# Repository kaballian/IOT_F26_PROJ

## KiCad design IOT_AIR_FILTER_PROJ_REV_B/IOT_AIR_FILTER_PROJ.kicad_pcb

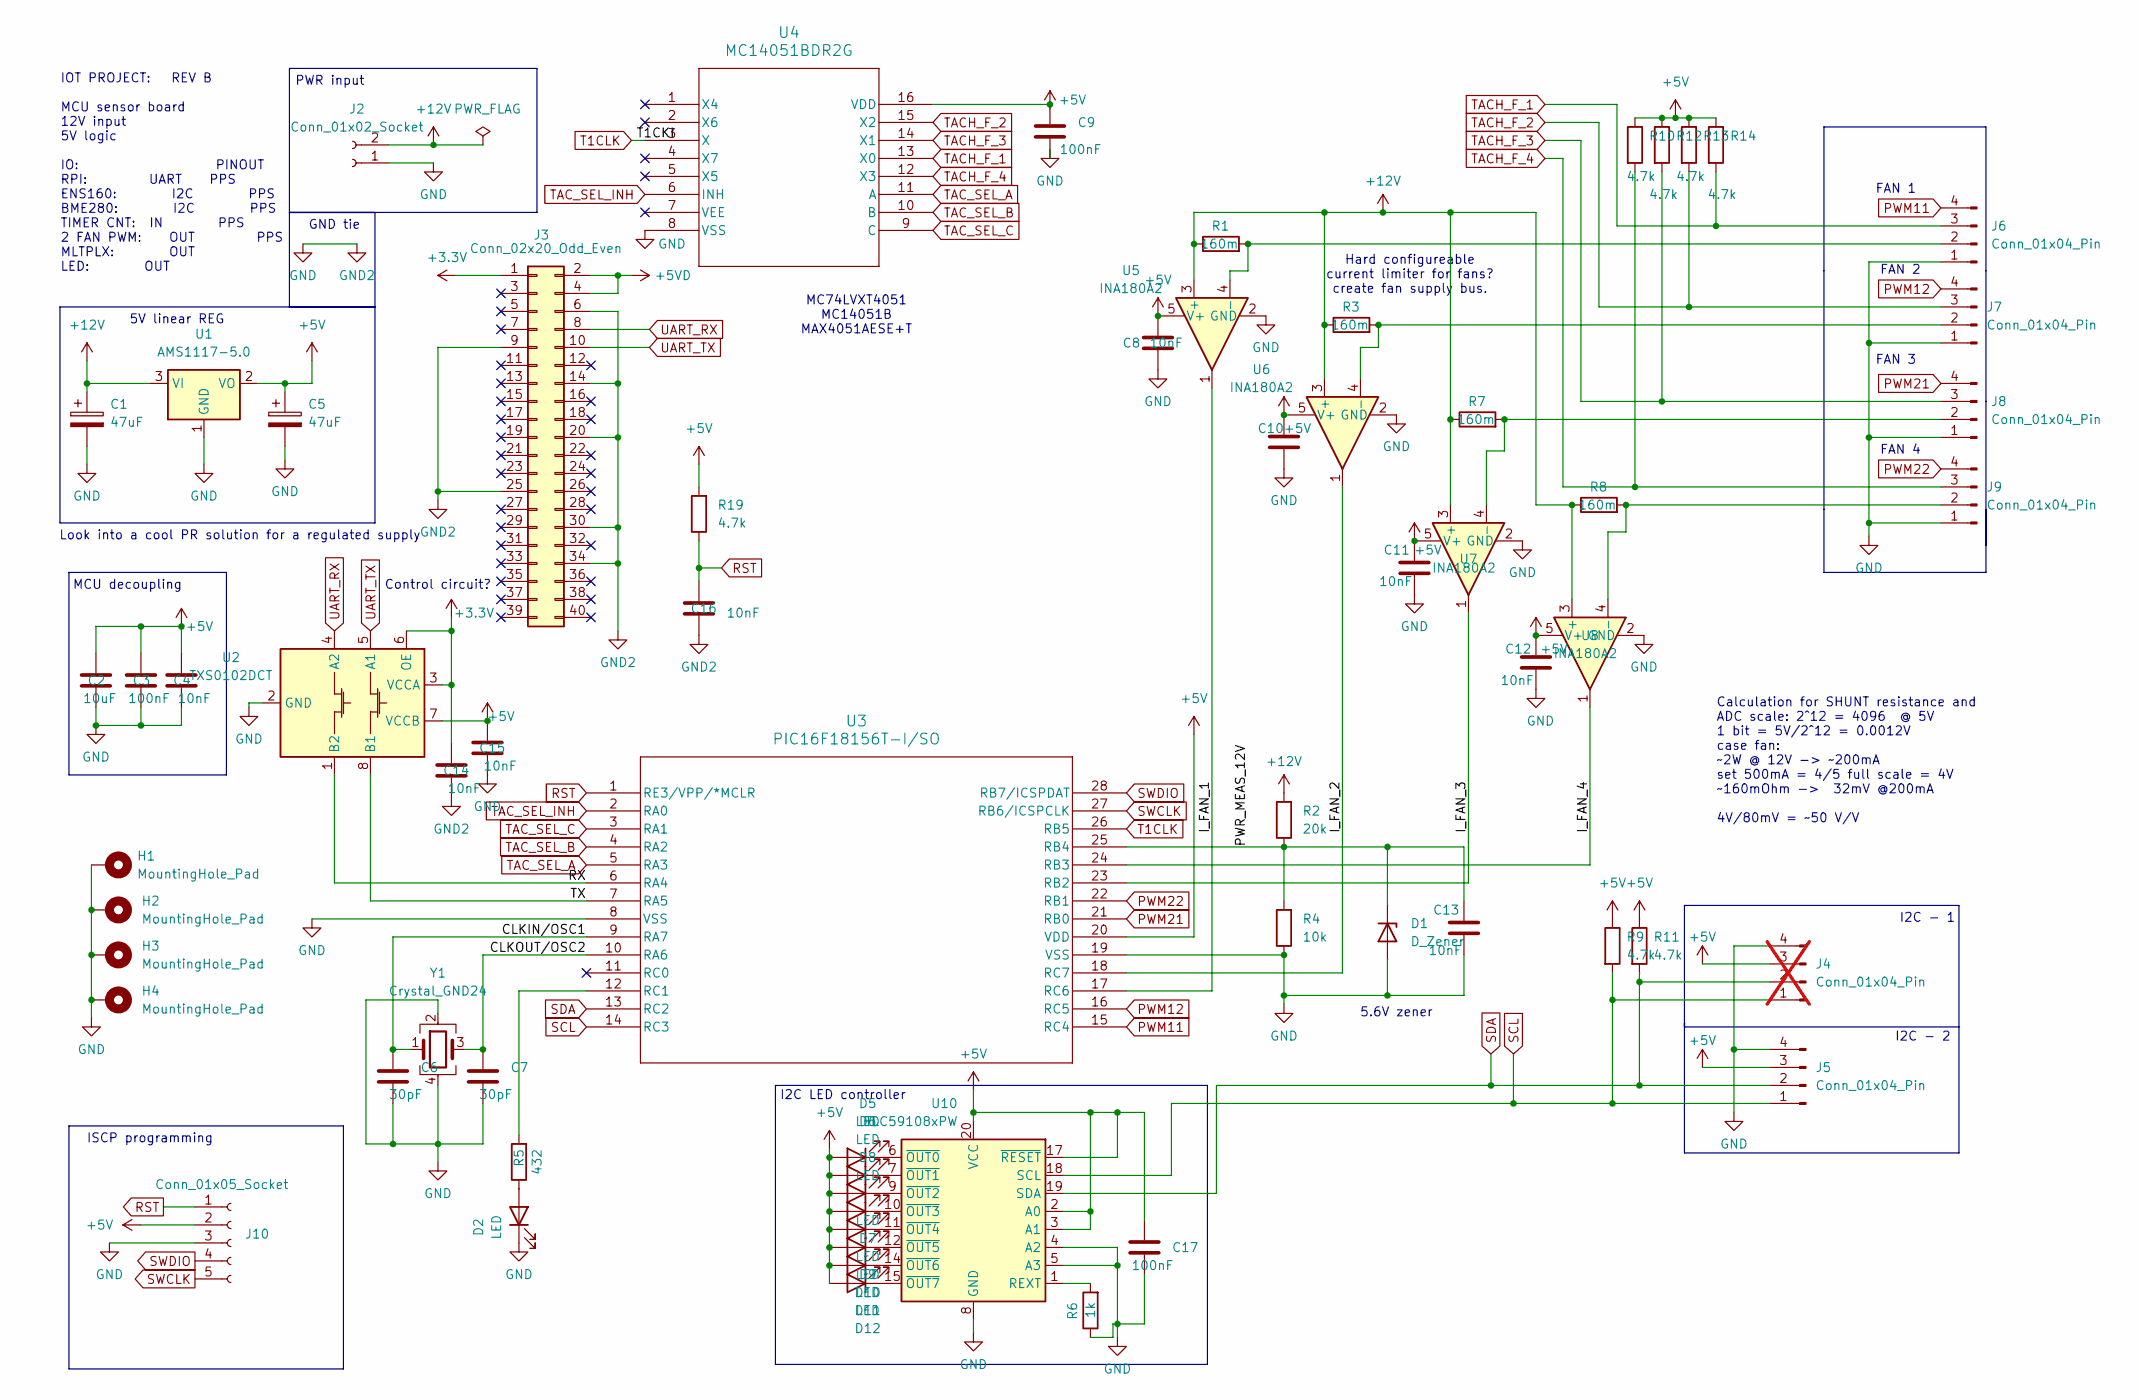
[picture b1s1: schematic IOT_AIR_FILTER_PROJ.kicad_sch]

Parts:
C1, C5: 47uF; CP_Elec_6.3x5.4
C2: 10uF; C_0805_2012Metric
C3, C9, C17: 100nF; C_0805_2012Metric
C4, C8, C10, C11, C12, C13, C14, C15, C16: 10nF; C_0805_2012Metric
C6, C7: 30pF; C_0805_2012Metric
D1: D_Zener; D_SOD-323
D2, D5, D6, D7, D8, D9, D10, D11, D12: LED; LED_0805_2012Metric_Pad1.15x1.40mm_HandSolder
H1, H2, H3, H4: MountingHole_Pad; MountingHole_2.5mm_Pad
J2: Conn_01x02_Socket; PinSocket_1x02_P2.54mm_Horizontal
J3: Conn_02x20_Odd_Even; PinSocket_2x20_P2.54mm_Vertical
J4: Conn_01x04_Pin; JST_GH_SM04B-GHS-TB_1x04-1MP_P1.25mm_Horizontal; not fitted
J5: Conn_01x04_Pin; JST_GH_SM04B-GHS-TB_1x04-1MP_P1.25mm_Horizontal
J6, J7, J8, J9: Conn_01x04_Pin; FanPinHeader_1x04_P2.54mm_Vertical
J10: Conn_01x05_Socket; JST_GH_SM05B-GHS-TB_1x05-1MP_P1.25mm_Horizontal
R1, R3, R7, R8: 160m; R_1210_3225Metric
R2: 20k; R_0805_2012Metric
R4: 10k; R_0805_2012Metric
R5: 432; R_0402_1005Metric
R6: 1k; R_1210_3225Metric
R9, R10, R11, R12, R13, R14, R19: 4.7k; R_0805_2012Metric
U1: AMS1117-5.0; SOT-223-3_TabPin2
U2: TXS0102DCT; SSOP-8_2.95x2.8mm_P0.65mm
U3: PIC16F18156T-I/SO; SOIC28_SO_MCH
U4: MC14051BDR2G; SOIC-16_ONS
U5, U6, U7, U8: INA180A2; SOT-23-5
U10: TLC59108xPW; TSSOP-20_4.4x6.5mm_P0.65mm
Y1: Crystal_GND24; Crystal_SMD_SeikoEpson_FA238-4Pin_3.2x2.5mm_HandSoldering

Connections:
+3.3V: C14.1, J3.1, U2.3 (VCCA), U2.6 (OE)
+5V: C2.1, C3.1, C4.1, C5.1, C8.1, C9.1, C10.1, C11.1, C12.1, C15.1, C17.1, D5.2 (A), D6.2 (A), D7.2 (A), D8.2 (A), D9.2 (A), D10.2 (A), D11.2 (A), D12.2 (A), J4.3, J5.3, J10.2, R9.1, R10.1, R11.1, R12.1, R13.1, R14.1, R19.2, U1.2 (VO), U2.7 (VCCB), U3.20 (VDD), U4.16 (VDD), U5.5 (V+), U6.5 (V+), U7.5 (V+), U8.5 (V+), U10.2 (A0), U10.3 (A1), U10.17 (~RESET), U10.20 (VCC)
+5VD: J3.2, J3.4
+12V: C1.1, J2.2, R1.1, R2.2, R3.1, R7.1, R8.1, U1.3 (VI), U5.3 (+), U6.3 (+), U7.3 (+), U8.3 (+)
/CLKIN/OSC1: C6.1, U3.9 (RA7), Y1.1
/CLKOUT/OSC2: C7.1, U3.10 (RA6), Y1.3
/I_FAN_1: U3.17 (RC6), U5.1
/I_FAN_2: U3.18 (RC7), U6.1
/I_FAN_3: U3.23 (RB2), U7.1
/I_FAN_4: U3.24 (RB3), U8.1
/PWR_MEAS_12V: C13.1, D1.1 (K), R2.1, R4.2, U3.25 (RB4)
/RX: U2.1 (B2), U3.6 (RA4)
/TX: U2.8 (B1), U3.7 (RA5)
GND: C1.2, C2.2, C3.2, C4.2, C5.2, C6.2, C7.2, C8.2, C9.2, C10.2, C11.2, C12.2, C13.2, C14.2, C15.2, C16.2, C17.2, D1.2 (A), D2.1 (K), H1.1, H2.1, H3.1, H4.1, J2.1, J3.6, J3.9, J3.14, J3.20, J3.25, J3.30, J3.34, J4.4, J5.4, J6.1, J7.1, J8.1, J9.1, J10.3, R4.1, R6.1, U1.1 (GND), U2.2 (GND), U3.8 (VSS), U3.19 (VSS), U4.8 (VSS), U5.2 (GND), U6.2 (GND), U7.2 (GND), U8.2 (GND), U10.4 (A2), U10.5 (A3), U10.8 (GND), U10.13 (GND), U10.16 (GND), Y1.2, Y1.4
unnamed: D2.2 (A), R5.1
unnamed: D5.1 (K), U10.6 (~OUT0)
unnamed: D6.1 (K), U10.7 (~OUT1)
unnamed: D7.1 (K), U10.9 (~OUT2)
unnamed: D8.1 (K), U10.10 (~OUT3)
unnamed: D9.1 (K), U10.11 (~OUT4)
unnamed: D10.1 (K), U10.12 (~OUT5)
unnamed: D11.1 (K), U10.14 (~OUT6)
unnamed: D12.1 (K), U10.15 (~OUT7)
unnamed: J6.2, R1.2, U5.4 (-)
unnamed: J7.2, R3.2, U6.4 (-)
unnamed: J8.2, R7.2, U7.4 (-)
unnamed: J9.2, R8.2, U8.4 (-)
unnamed: R5.2, U3.12 (RC1)
unnamed: R6.2, U10.1 (REXT)
PWM11: J6.4, U3.15 (RC4)
PWM12: J7.4, U3.16 (RC5)
PWM21: J8.4, U3.21 (RB0)
PWM22: J9.4, U3.22 (RB1)
RST: C16.1, J10.1, R19.1, U3.1 (RE3/VPP/*MCLR)
SCL: J4.1, J5.1, R9.2, U3.14 (RC3), U10.18 (SCL)
SDA: J4.2, J5.2, R11.2, U3.13 (RC2), U10.19 (SDA)
SWCLK: J10.5, U3.27 (RB6/ICSPCLK)
SWDIO: J10.4, U3.28 (RB7/ICSPDAT)
T1CLK: U3.26 (RB5), U4.3 (X)
TACH_F_1: J6.3, R14.2, U4.13 (X0)
TACH_F_2: J7.3, R13.2, U4.15 (X2)
TACH_F_3: J8.3, R12.2, U4.14 (X1)
TACH_F_4: J9.3, R10.2, U4.12 (X3)
TAC_SEL_A: U3.5 (RA3), U4.11 (A)
TAC_SEL_B: U3.4 (RA2), U4.10 (B)
TAC_SEL_C: U3.3 (RA1), U4.9 (C)
TAC_SEL_INH: U3.2 (RA0), U4.6 (INH)
UART_RX: J3.8, U2.4 (A2)
UART_TX: J3.10, U2.5 (A1)

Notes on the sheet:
GND tie
5.6V zener
Calculation for SHUNT resistance and ADC scale: 2^12 = 4096 @ 5V 1 bit = 5V/2^12 = 0.0012V case fan: ~2W @ 12V -> ~200mA set 500mA = 4/5 full scale = 4V ~160mOhm -> 32mV @200mA 4V/80mV = ~50 V/V
MCU decoupling
FAN 1
FAN 2
FAN 4
5V linear REG
Look into a cool PR solution for a regulated supply
MC74LVXT4051 MC14051B MAX4051AESE+T
PWR input
Control circuit?
Hard configureable current limiter for fans? create fan supply bus.
IOT PROJECT: REV B MCU sensor board 12V input 5V logic IO: PINOUT RPI: UART PPS ENS160: I2C PPS BME280: I2C PPS TIMER CNT: IN PPS 2 FAN PWM: OUT PPS MLTPLX: OUT LED: OUT
I2C - 1
ISCP programming
I2C LED controller
I2C - 2
FAN 3

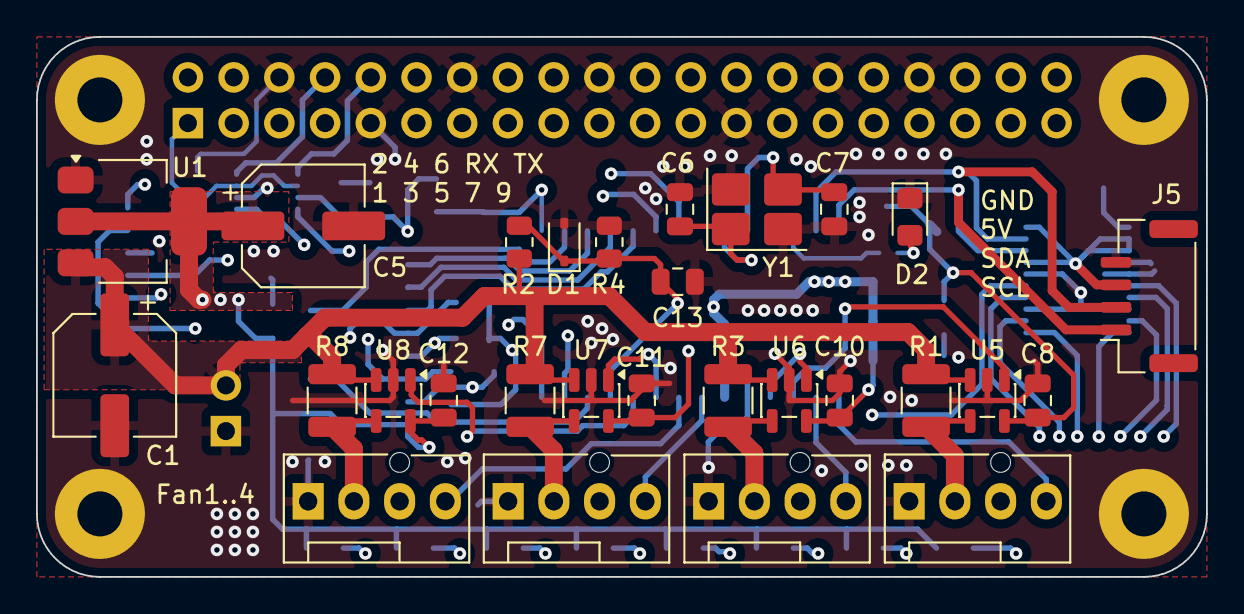
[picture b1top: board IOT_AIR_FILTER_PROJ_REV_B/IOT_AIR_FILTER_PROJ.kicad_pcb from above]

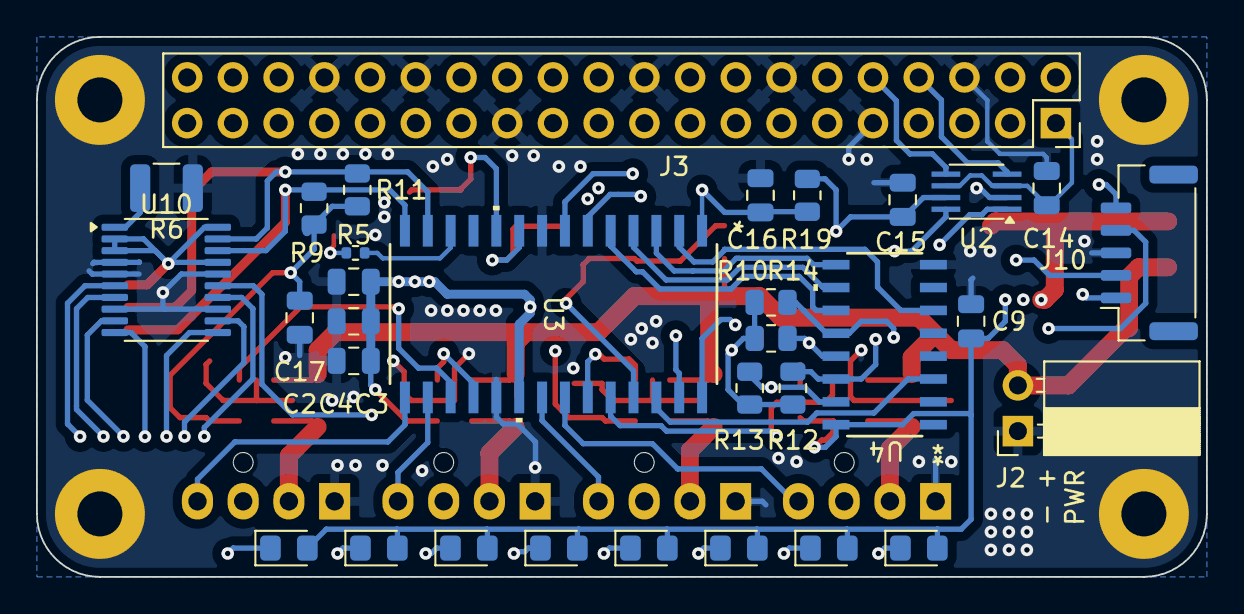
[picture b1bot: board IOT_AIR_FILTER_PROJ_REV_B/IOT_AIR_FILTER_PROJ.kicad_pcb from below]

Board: 4 copper layers, 65.0 x 30.0 mm, 64 parts (32 on the bottom side), 49 nets.

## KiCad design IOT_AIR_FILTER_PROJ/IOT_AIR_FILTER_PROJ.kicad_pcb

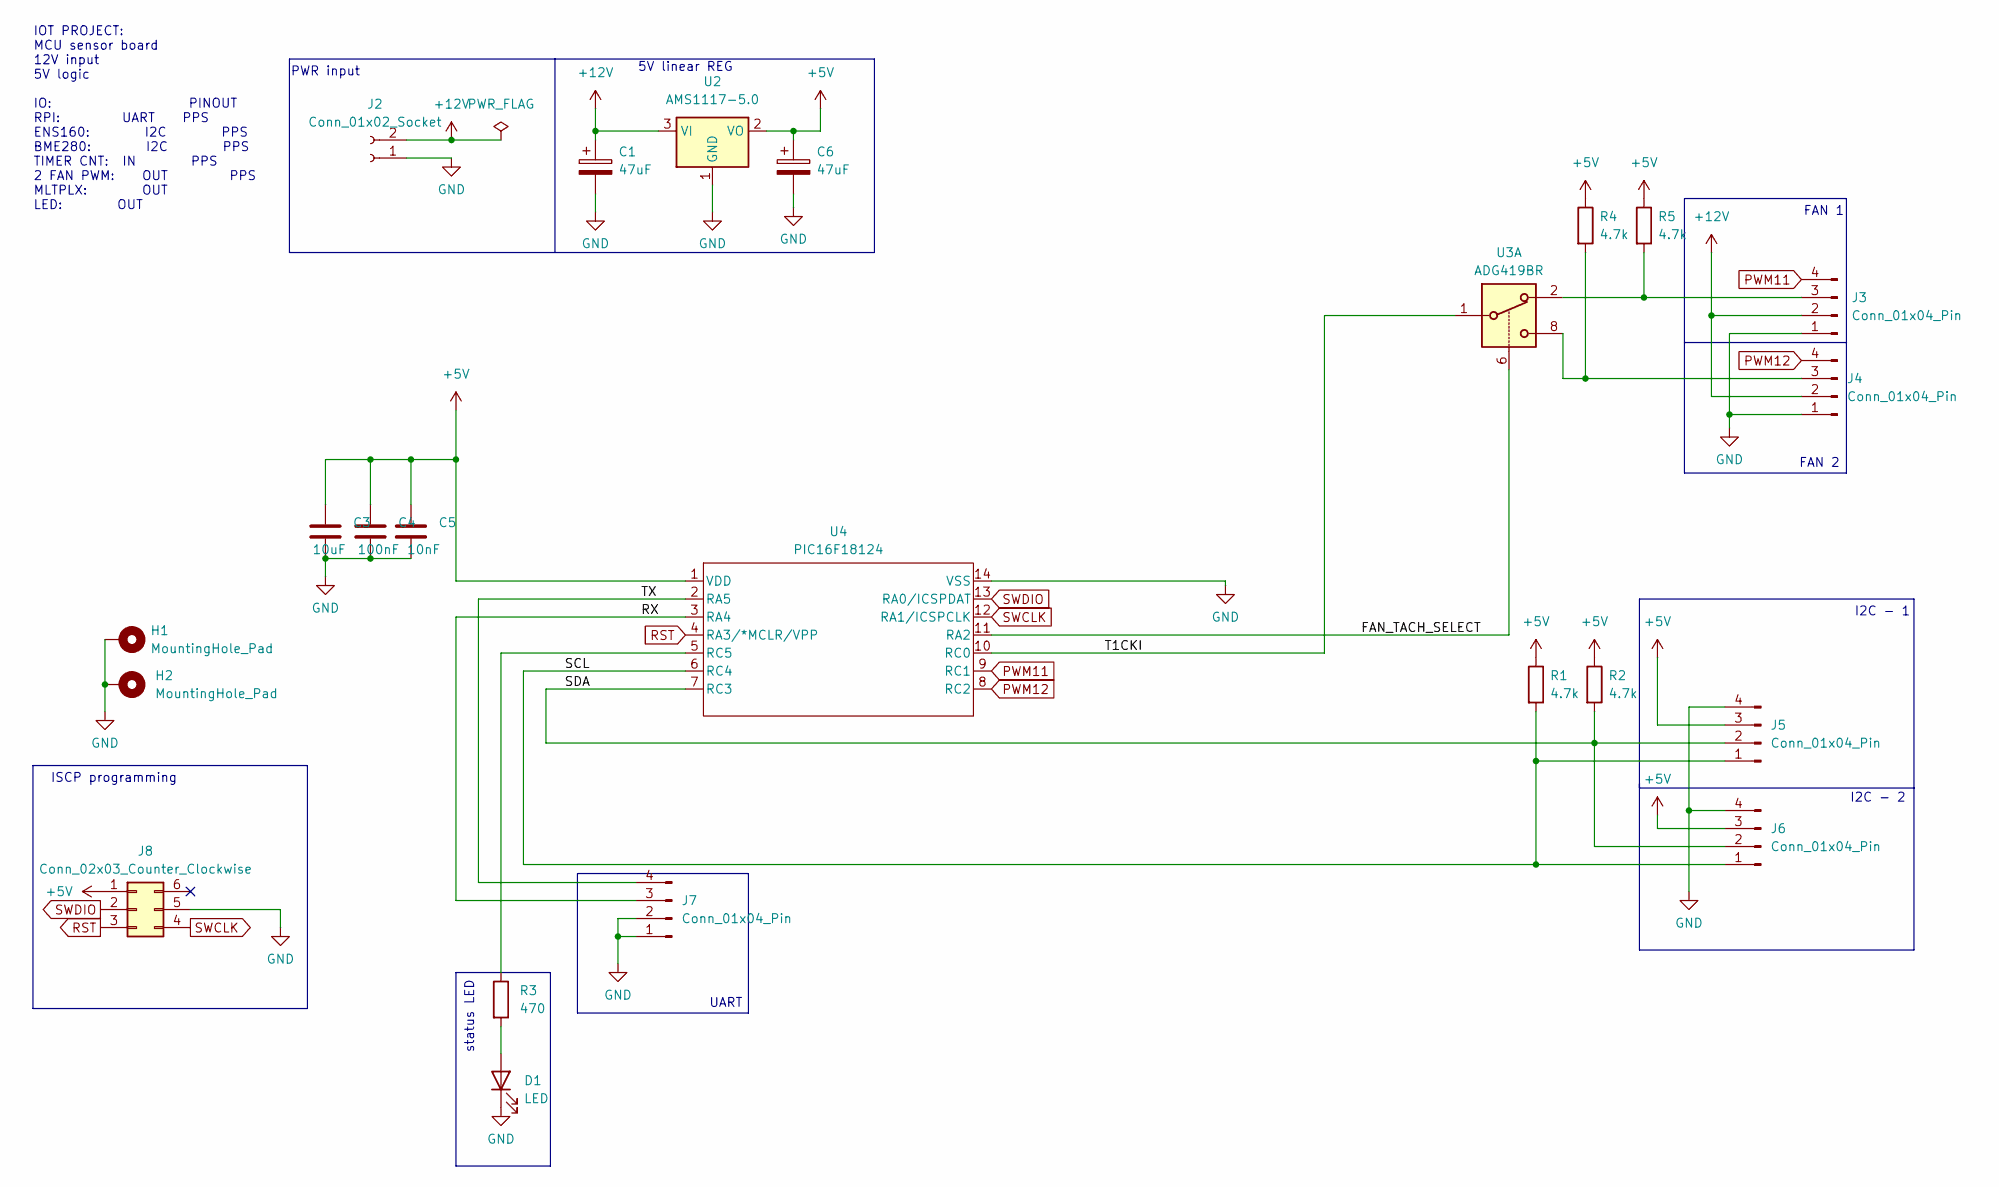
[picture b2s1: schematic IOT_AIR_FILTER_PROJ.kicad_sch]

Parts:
C1, C6: 47uF; CP_Elec_6.3x5.4
C3: 10uF; C_0805_2012Metric
C4: 100nF; C_0805_2012Metric
C5: 10nF; C_0805_2012Metric
D1: LED; LED_0805_2012Metric
H1, H2: MountingHole_Pad; MountingHole_3.2mm_M3_Pad
J2: Conn_01x02_Socket; PinSocket_1x02_P2.54mm_Horizontal
J3, J4: Conn_01x04_Pin; FanPinHeader_1x04_P2.54mm_Vertical
J5, J6, J7: Conn_01x04_Pin; PinHeader_1x04_P2.54mm_Vertical
J8: Conn_02x03_Counter_Clockwise; PinSocket_2x03_P2.54mm_Vertical
R1, R2, R4, R5: 4.7k; R_0805_2012Metric
R3: 470; R_0805_2012Metric
U2: AMS1117-5.0; SOT-223-3_TabPin2
U3: ADG419BR; SOIC-8_3.9x4.9mm_P1.27mm
U4: PIC16F18124; DIP-14_W7.62mm

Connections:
+5V: C3.1, C4.1, C5.1, C6.1, J5.3, J6.3, J8.1, R1.1, R2.1, R4.1, R5.1, U2.2 (VO), U4.1 (VDD)
+12V: C1.1, J2.2, J3.2, J4.2, U2.3 (VI)
/FAN_TACH_SELECT: U3.6, U4.11 (RA2)
/RX: J7.3, U4.3 (RA4)
/SCL: J5.1, J6.1, R1.2, U4.6 (RC4)
/SDA: J5.2, J6.2, R2.2, U4.7 (RC3)
/T1CKI: U3.1, U4.10 (RC0)
/TX: J7.4, U4.2 (RA5)
GND: C1.2, C3.2, C4.2, C5.2, C6.2, D1.1 (K), H1.1, H2.1, J2.1, J3.1, J4.1, J5.4, J6.4, J7.1, J7.2, J8.5, U2.1 (GND), U4.14 (VSS)
unnamed: D1.2 (A), R3.2
unnamed: J3.3, R5.2, U3.2
unnamed: J4.3, R4.2, U3.8
unnamed: R3.1, U4.5 (RC5)
PWM11: J3.4, U4.9 (RC1)
PWM12: J4.4, U4.8 (RC2)
RST: J8.3, U4.4 (RA3/*MCLR/VPP)
SWCLK: J8.4, U4.12 (RA1/ICSPCLK)
SWDIO: J8.2, U4.13 (RA0/ICSPDAT)

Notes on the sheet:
UART
FAN 1
FAN 2
5V linear REG
status LED
PWR input
IOT PROJECT: MCU sensor board 12V input 5V logic IO: PINOUT RPI: UART PPS ENS160: I2C PPS BME280: I2C PPS TIMER CNT: IN PPS 2 FAN PWM: OUT PPS MLTPLX: OUT LED: OUT
I2C - 1
ISCP programming
I2C - 2

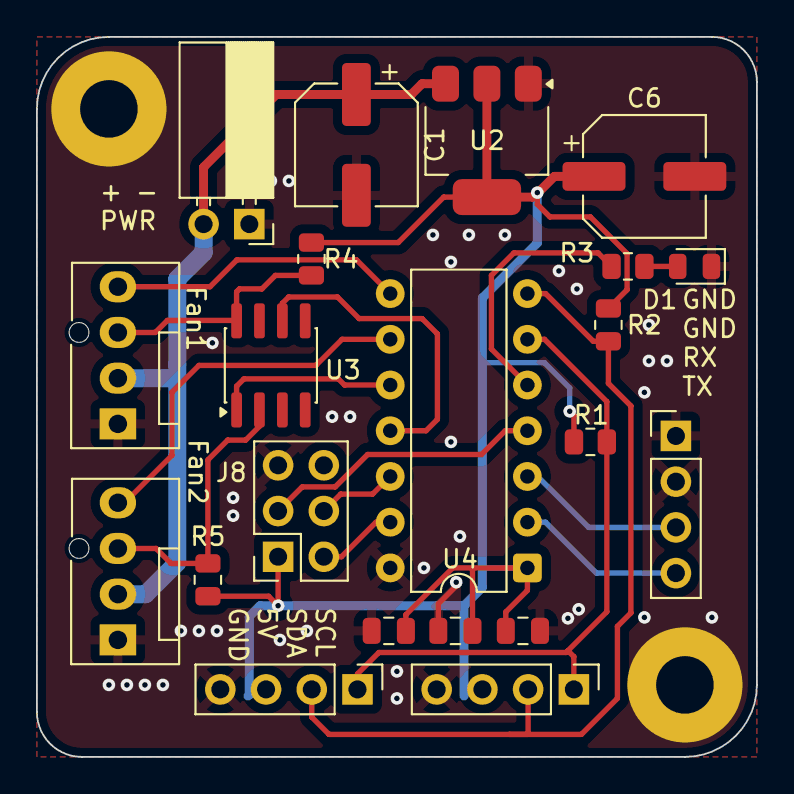
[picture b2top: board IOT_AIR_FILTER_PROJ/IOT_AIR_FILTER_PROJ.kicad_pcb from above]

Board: 2 copper layers, 40.0 x 40.0 mm, 23 parts (0 on the bottom side), 18 nets.

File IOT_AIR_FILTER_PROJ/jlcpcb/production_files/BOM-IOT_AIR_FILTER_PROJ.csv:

Comment,Designator,Footprint,LCSC,Quantity
100nF,C4,C_0805_2012Metric,C49678,1
10nF,C5,C_0805_2012Metric,C1710,1
10uF,C3,C_0805_2012Metric,C440198,1
4.7k,"R1,R2,R4,R5",R_0805_2012Metric,C17673,4
470,R3,R_0805_2012Metric,C17710,1
47uF,"C1,C6",CP_Elec_6.3x5.4,C7469965,2
ADG419BR,U3,SOIC-8_3.9x4.9mm_P1.27mm,C579051,1
AMS1117-5.0,U2,SOT-223-3_TabPin2,C6187,1
LED,D1,LED_0805_2012Metric,C2296,1

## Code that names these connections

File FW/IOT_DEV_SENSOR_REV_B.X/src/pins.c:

#include "include\pins.h"
#include <pic16f18156.h>

void PIN_MANAGER_init(void)
{
    /*LATx registers*/

    LATA = 0x0;
    LATB = 0x0;
    LATC = 0x0;

    /*TRISx registers
    1: input
    0: output
    
    PORT    = |FUNCTION|DIRECTION|VAL|PPS
    RA0     = TAC_SEL_INH   OUT X
    RA1     = TAC_SEL_C     OUT
    RA2     = TAC_SEL_B     OUT
    RA3     = TAC_SEL_A     OUT
    RA4     = RX            IN  1   PPS
    RA5     = TX            OUT 0   PPS

    RB0     = PWM21         OUT 0   PPS
    RB1     = PWM22         OUT 0   PPS
    RB2     = I_FAN_3       IN  1   
    RB3     = I_FAN_4       IN  1
    RB4     = PWR_MEAS_12V  IN  1
    RB5     = T1CLKIN       IN  1   PPS
    
    RC0     = unconnected           
    RC1     = unconnected
    RC2     = I2C SDA       BI      PPS
    RC3     = I2C SCL       BI      PPS
    RC4     = PWM11         OUT 0   PPS
    RC5     = PWM12         OUT 0   PPS
    RC6     = I_FAN_1       IN  1    
    RC7     = I_FAN_2       IN  1


    */

    TRISAbits.TRISA0 = 0;
    TRISAbits.TRISA1 = 0;
    TRISAbits.TRISA2 = 0;
    TRISAbits.TRISA3 = 0;
    TRISAbits.TRISA4 = 1;
    TRISAbits.TRISA5 = 0;

    TRISBbits.TRISB0 = 0;// RB0     = PWM21         OUT 0   PPS
    TRISBbits.TRISB1 = 0;// RB1     = PWM22         OUT 0   PPS
    TRISBbits.TRISB2 = 1;// RB2     = I_FAN_3       IN  1   
    TRISBbits.TRISB3 = 1;// RB3     = I_FAN_4       IN  1
    TRISBbits.TRISB4 = 1;// RB4     = PWR_MEAS_12V  IN  1
    TRISBbits.TRISB5 = 1;// RB5     = T1CLKIN       IN  1   PPS
    
    // TRISCbits.TRISC// RC0     = unconnected  MAKE HI Z           
    // TRISCbits.TRISC// RC1     = unconnected  MAKE HI Z
    TRISCbits.TRISC2 = 1;// RC2     = I2C SDA       BI      PPS
    TRISCbits.TRISC3 = 1;// RC3     = I2C SCL       BI      PPS
    TRISCbits.TRISC4 = 0;// RC4     = PWM11         OUT 0   PPS
    TRISCbits.TRISC5 = 0;// RC5     = PWM12         OUT 0   PPS
    TRISCbits.TRISC6 = 1;// RC6     = I_FAN_1       IN  1    
    TRISCbits.TRISC7 = 1;// RC7     = I_FAN_2       IN  1

    /*ANSELx registers
    analog control
    1 = analog input
    0 = digital i/o*/
    ANSELAbits.ANSELA0 = 0;
    ANSELAbits.ANSELA1 = 0;
    ANSELAbits.ANSELA2 = 0;
    ANSELAbits.ANSELA3 = 0;
    ANSELAbits.ANSELA4 = 0;
    ANSELAbits.ANSELA5 = 0;

    ANSELBbits.ANSELB0 = 0;
    ANSELBbits.ANSELB1 = 0;
    ANSELBbits.ANSELB2 = 1; //ADC
    ANSELBbits.ANSELB3 = 1; //ADC
    ANSELBbits.ANSELB4 = 1; //ADC
    ANSELBbits.ANSELB5 = 0;

    // ANSELCbits.ANSELC0 = 0; unconnected
    // ANSELCbits.ANSELC1 = 0; unconnected
    ANSELCbits.ANSELC2 = 0;
    ANSELCbits.ANSELC3 = 0;
    ANSELCbits.ANSELC4 = 0;
    ANSELCbits.ANSELC5 = 0;
    ANSELCbits.ANSELC6 = 1; //ADC
    ANSELCbits.ANSELC7 = 1; //ADC

    /* weak pull ups*/
    WPUA = 0x0;
    WPUB = 0x0;
    WPUC = 0x0;

    /*open drain control*/
    ODCONA = 0x0;
    ODCONB = 0x0;
    ODCONC = 0x0;

    /*slew rate*/
    SLRCONBbits.SLRB2 = 0;
    SLRCONBbits.SLRB3 = 0;

    /*input level: schmitt trigger*/
    INLVLBbits.INLVLB2 = 1;
    INLVLBbits.INLVLB3 = 1;

    // PPS
    /*note for I2C: bidirectional pins, SDA/SCL must be mapped to same pin*/

    /*unlock sequence*/
    INTCONbits.GIE = 0;
    PPSLOCK = 0x55;
    PPSLOCK = 0xAA;
    PPSLOCKbits.PPSLOCKED = 0;
    INTCONbits.GIE = 1;
    /*remap sequence*/
    /*
    note section 18.8.1 xxxPPS ("XXX" = any PPS inpuit register from table 18-1)
    xxxPPS[5:3] => PORT[2:0] -> peripheral input PORT selection 
    xxxPPS[2:0] => PIN[2:0] -> peripheral input PIN selection*/
    /*inputs*/
    RX1PPS      = 0b00000100; // 0b00|[000:PORTA]|[100:PORTxPin4]
    T1CKIPPS    = 0b00001101; // 0b00|[001:PORTB]|[101:PORTxPin5]
    SSP2DATPPS  = 0b00010010; // 0b00|[010:PORTC]|[010:PORTxPin2]
    SSP2CLKPPS  = 0b00010011; // 0b00|[010:PORTC]|[011:PORTxPin3]

    /*outputs*/
    /*RxyPPS[5:0] <- entry from table[18-2] */
    RA5PPS = 0x13; //TX
    RC4PPS = 0x0B; //PWM11
    RC5PPS = 0x0C; //PWM12
    RB0PPS = 0x0D; //PWM13
    RB1PPS = 0x0E; //PWM14
    RC2PPS = 0x1E; //SDA2
    RC3PPS = 0x1D; //SCL2


    /*lock sequence*/
    INTCONbits.GIE = 0;
    PPSLOCK = 0x55;
    PPSLOCK = 0xAA;
    PPSLOCKbits.PPSLOCKED = 1;
    INTCONbits.GIE = 1;

};

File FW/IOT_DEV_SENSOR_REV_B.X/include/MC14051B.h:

#ifndef MC14051_H
#define MC14051_H

#include "include/utils.h"

//number of channels
#define MC14051_CHLS 4
//pin selections (naming convention from schematic)
#define TAC_SEL_INH     ((pin_t){.lat=&LATA, .tris=&TRISA, .bitmask=(1u<<RA0)})
#define TAC_SEL_C       ((pin_t){.lat=&LATA, .tris=&TRISA, .bitmask=(1u<<RA1)})
#define TAC_SEL_B       ((pin_t){.lat=&LATA, .tris=&TRISA, .bitmask=(1u<<RA2)})
#define TAC_SEL_A       ((pin_t){.lat=&LATA, .tris=&TRISA, .bitmask=(1u<<RA3)})

#define TAC_SEL_MASK \ (TAC_SEL_A.bitmask | TAC_SEL_B.bitmask | TAC_SEL_C.bitmask)

typedef enum{
    CHL_1 = 0,
    CHL_2 = 1,
    CHL_3 = 2,
    CHL_4 = 3,
}switch_chl_t;

typedef struct{
    switch_chl_t    status;
    pin_t           inhibit;
    pin_t           sel_A;
    pin_t           sel_B;
    pin_t           sel_C;

}MC14051_t;


void MC14051_init(MC14051_t *dev);
void MC14051_CHL_SELECT(MC14051_t *dev, switch_chl_t chl);
void MC14051_INHIB_ON(MC14051_t *dev);
void MC14051_INHIB_OFF(MC14051_t *dev);

#endif

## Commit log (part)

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2026-03-22 completed proposal
2026-03-24 GIT cleanup
2026-03-24 schematic design and layout for IOT device
2026-03-25 minor changes to schematic, component selection and layout
2026-03-29 added schematics/layout/manufacturing files. Also initial FW for IOT sensor
2026-03-30 work into sensor
2026-03-31 pins.h/.c definition
2026-03-31 EUSART progress
2026-04-02 defined FAN and PWM
2026-04-02 completed generic I2C driver
2026-04-02 progress into ENS160 driver
2026-04-03 complete I2C driver for ENS160
2026-04-03 complete driver for ADG419BR SPDT switch
2026-04-03 progress into SM integration
2026-04-04 rewritten FSM dispatch and transition and added a .c demo for the statemachine, which can be ran in GODBOLT
2026-04-04 TMR1 as counter
2026-04-04 implementation of FAN measurement routing
2026-04-04 completed minor systems, integration hell time
2026-04-05 queue system for layered application, also safepoint before entry starts, handler reacts style FSM for fans
2026-04-05 major steps into application and FSM integration
2026-04-18 updates to hardware layout. Sent to faprication
2026-04-18 working of APP layer
2026-04-19 application layer for i2c measurement done. TX ISR is next
2026-04-21 added states and functions protos to set fan speed
2026-04-21 reworded UART RX function and parser structure with statemachine
2026-04-24 app_service progress, completed set fan service and FSM
2026-04-25 completed 3 UART TX scenarios, and implemented frame assember
2026-04-26 MCU code is somewhat complete now
2026-05-04 added raspberry pi stuff
2026-05-14 mayor progress in integration, PWM, TMR0/1, I2C, UART is working
2026-05-15 trying to rescue program space
2026-05-15 major changes to FSM and app_service()
2026-05-16 ITS WORKING
2026-05-16 timeout faults has been remedied
2026-05-17 report created
2026-05-18 working on sys arch
2026-05-22 minor changes to UART reply
2026-05-24 added mqtt gateway script
2026-05-24 added gitignore to avoid VENV inclusions
